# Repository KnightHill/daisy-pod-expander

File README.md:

# POD Expander

Expander board for the [ElectroSmith POD](https://www.electro-smith.com/daisy/pod)

## OLED Expander (v 1.1)

Final version of the expander, adding OLED display, two potentiometers, and one button.
Firmware, KiCad 7 project and Gerber files included.

## List of parts
- 1 16 pin female header
- 1 7 pin female header
- 2 [10k potentiometers](https://www.amazon.com/uxcell-Carbon-Potentiometer-Variable-Resistors/dp/B07STNVSC3)
- 1 [tactile switch](https://www.amazon.com/QTEATAK-Momentary-Tactile-Button-Switch/dp/B07VSNN9S2/)
- 1 [OLED SPI display (SSD1306)](https://www.amazon.com/HiLetgo-Serial-128X64-Display-Color/dp/B01MQPQF24/)

## PCB

## Populated board

 # Disclamer

This is a hobby project. I am not affiliated with ElectroSmith in any way. I accept no responsibility for damage to you Daisy Seed, external equipment or anything else. You use this code and hardware at your own risk. All names, logos, images, and brands are property of their respective owners.

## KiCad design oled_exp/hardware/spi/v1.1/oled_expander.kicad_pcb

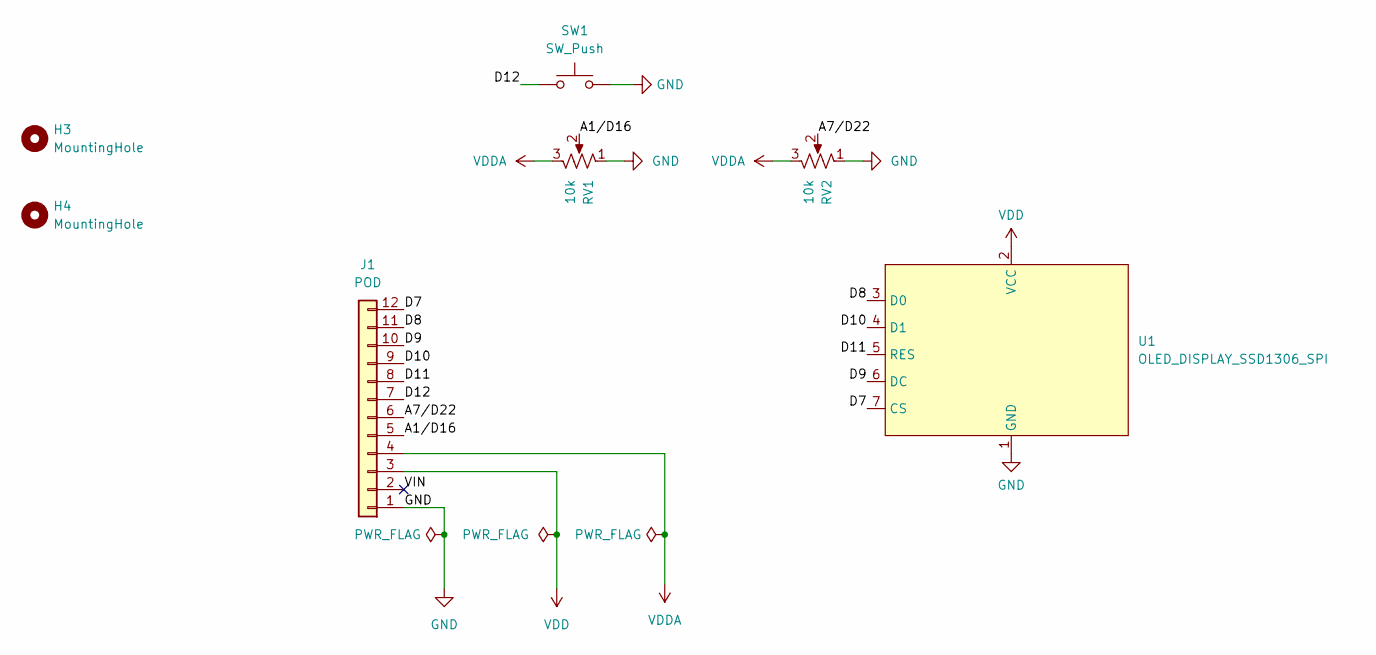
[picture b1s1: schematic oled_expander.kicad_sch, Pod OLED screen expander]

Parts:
H3, H4: MountingHole; MountingHole_2.2mm_M2
J1: POD; PinSocket_1x12_P2.54mm_Vertical
RV1, RV2: 10k; Potentiometer_uxcel_9mm_Single_Vertical
SW1: SW_Push; SW_PUSH_6mm
U1: OLED_DISPLAY_SSD1306_SPI; HiLetgo_OLED_SPI

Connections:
/A1/D16: J1.5, RV1.2
/A7/D22: J1.6, RV2.2
/D7: J1.12, U1.7 (CS)
/D8: J1.11, U1.3 (D0)
/D9: J1.10, U1.6 (DC)
/D10: J1.9, U1.4 (D1)
/D11: J1.8, U1.5 (RES)
/D12: J1.7, SW1.1
/VIN: J1.2
GND: J1.1, RV1.1, RV2.1, SW1.2, U1.1 (GND)
VDD: J1.3, U1.2 (VCC)
VDDA: J1.4, RV1.3, RV2.3

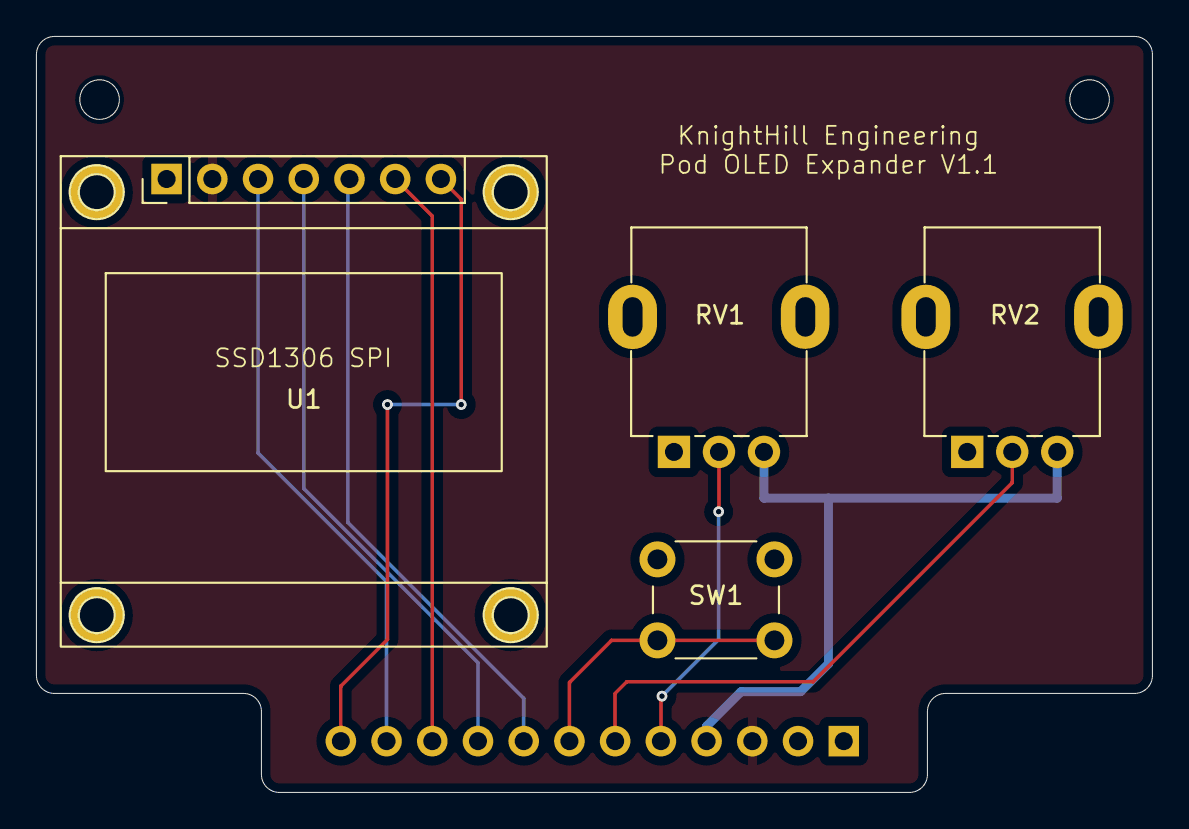
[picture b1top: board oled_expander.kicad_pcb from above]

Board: 2 copper layers, 62.0 x 42.0 mm, 7 parts (1 on the bottom side), 11 nets.

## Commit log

2024-06-17 ignore backups
2024-06-19 add parts
2024-06-19 add links
2024-06-19 readme changes
